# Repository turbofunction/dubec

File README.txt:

Contact:
Janne Savukoski
<firstname>@savukoski.name

                    Part name: DUBEC
                     Revision: 2.3
                   Board size: 40mm x 21.375mm
              Board thickness: 
                   Board type: Four layer
       Outer copper thickness:
       Inner copper thickness:
Solder mask color (top & bot):
 Silkscreen color (top & bot):

No special instructions.

Layer order:

TOP:    DUBEC.toplayer.ger
        DUBEC.internalplane1.ger
        DUBEC.internalplane2.ger
BOTTOM: DUBEC.bottomlayer.ger

Other files:

DUBEC.boardoutline.ger     Outline
DUBEC.topsoldermask.ger    Solder mask TOP
DUBEC.bottomsoldermask.ger Solder mask BOTTOM
DUBEC.topsilkscreen.ger    Silkscreen TOP
DUBEC.bottomsilkscreen.ger Silkscreen BOTTOM
DUBEC.drills.xln           Excellon drill
DUBEC.drl                  Drill rack
DUBEC.tcream.ger           Solder stencil (TOP)

Thank you!

Regards,
Janne Savukoski

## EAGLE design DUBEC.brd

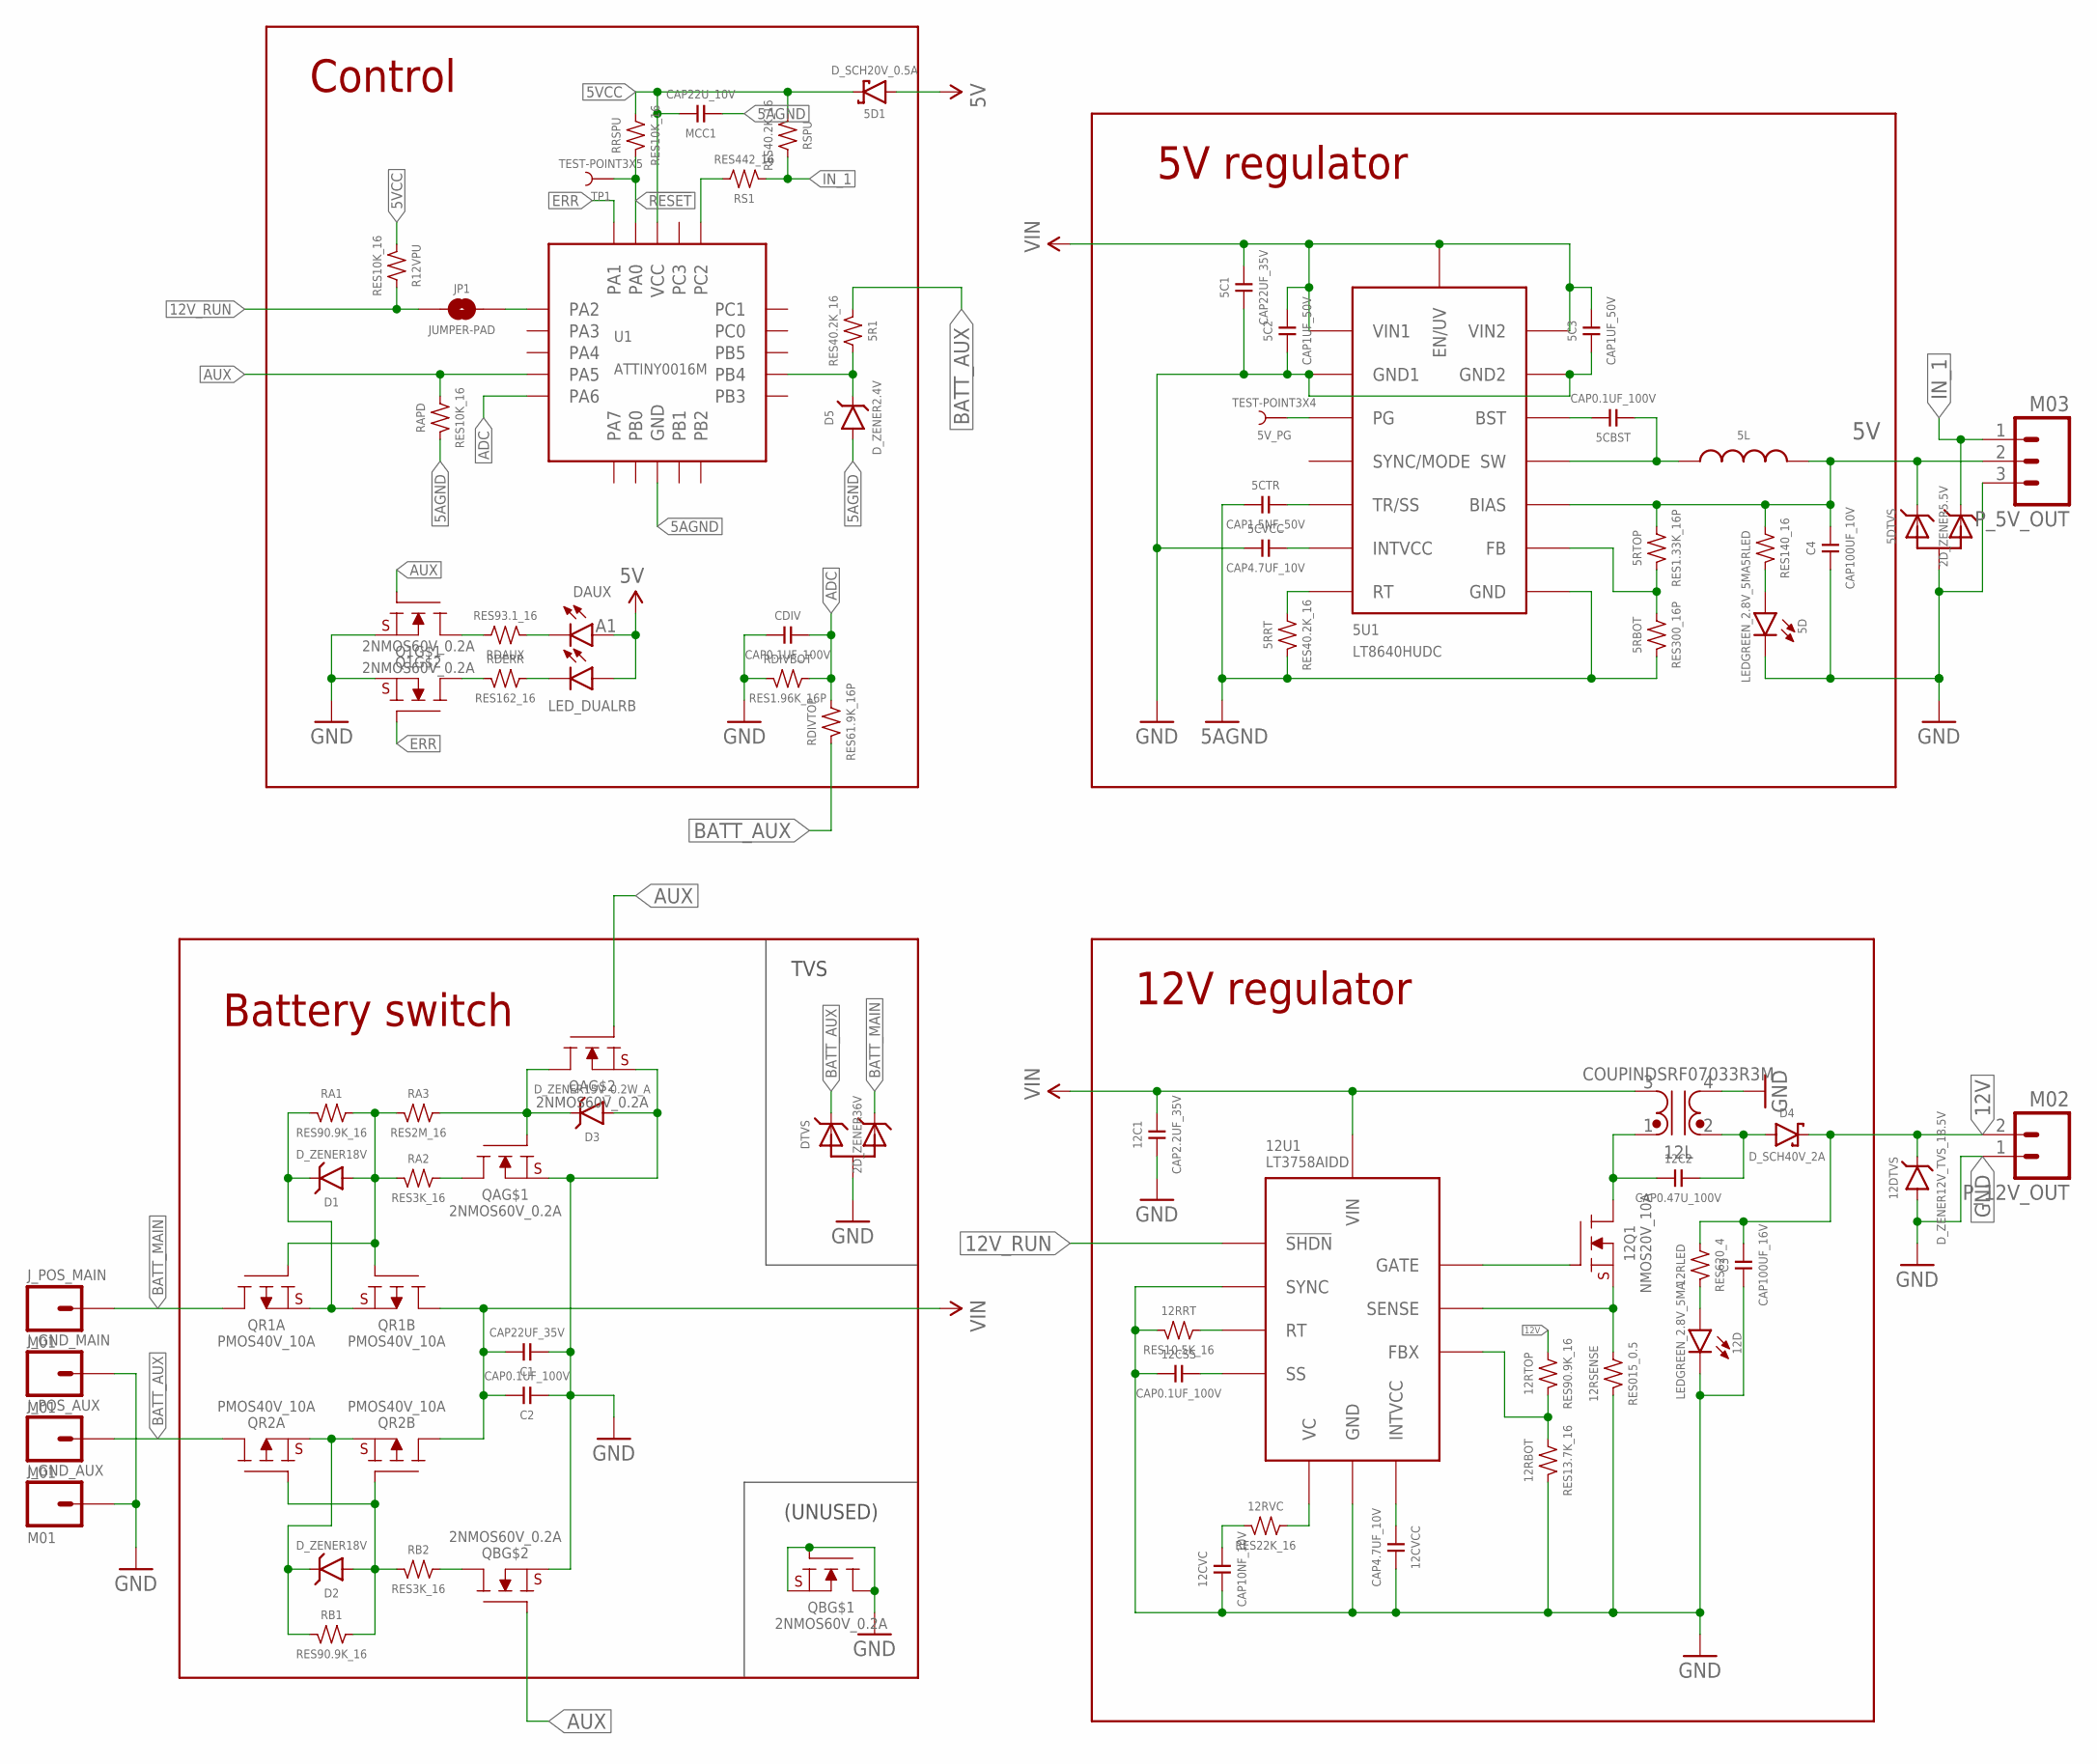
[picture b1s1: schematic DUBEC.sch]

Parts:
5C1: CAP22UF_35V; 0805
5C2, 5C3: CAP1UF_50V; 0603
5CBST, 12CSS: CAP0.1UF_100V; 0402
5CTR: CAP1.5NF_50V; 0402
5CVCC, 12CVCC: CAP4.7UF_10V; 0402
5D, 12D: LEDGREEN_2.8V_5MA; 0603+
5D1: D_SCH20V_0.5A; SOD523+
5DTVS: 2D_ZENER5.5V; SOT23-3
5L: I3.3UH_5A; SRP5030
5R1, 5RRT: RES40.2K_16; 0402
5RBOT: RES300_16P; 0402
5RLED: RES140_16; 0402
5RTOP: RES1.33K_16P; 0402
5U1: LT8640HUDC; QFN-18
5V_PG: TEST-POINT3X4; PAD.03X.04
12C1: CAP2.2UF_35V; 0402
12C2: CAP0.47U_100V; 0805
12CVC: CAP10NF_10V; 0402
12DTVS: D_ZENER12V_TVS_18.5V; SOD323+
12L: COUPINDSRF07033R3M; SRF0703
12Q1: NMOS20V_10A; 6-PQFN
12RBOT: RES13.7K_16; 0402
12RLED: RES620_4; 0603
12RRT: RES10.5K_16; 0402
12RSENSE: RES015_0.5; 1206
12RTOP: RES90.9K_16; 0402
12RVC: RES22K_16; 0402
12U1: LT3758AIDD; DFN-10
C1: CAP22UF_35V; 0805
C2: CAP0.1UF_100V; 0402
C3: CAP100UF_16V; 1210
C4: CAP100UF_10V; 1210
CDIV: CAP0.1UF_100V; 0402
D1, D2: D_ZENER18V; SOD523+
D3: D_ZENER15V_0.2W_A; SOD523+
D4: D_SCH40V_2A; DO-214AC
D5: D_ZENER2.4V; SOD523+
DAUX: LED_DUALRB; 0603+DUAL
DTVS: 2D_ZENER36V; SOT23-3
JP1: JUMPER-PAD; JUMPER-PAD-ROUND
J_GND_AUX: M01; 1X01_NO_SILK
J_GND_MAIN: M01; 1X01_NO_SILK
J_POS_AUX: M01; 1X01_NO_SILK
J_POS_MAIN: M01; 1X01_NO_SILK
MCC1: CAP22U_10V; 0603
P_5V_OUT: M03; 1X03_NO_SILK
P_12V_OUT: M02; 1X02_NO_SILK
Q1: 2NMOS60V_0.2A; SOT-666
QA: 2NMOS60V_0.2A; SOT-666
QB: 2NMOS60V_0.2A; SOT-666
QR1A, QR1B, QR2A, QR2B: PMOS40V_10A; POWERDI3333-8
R12VPU: RES10K_16; 0402
RA1: RES90.9K_16; 0402
RA2: RES3K_16; 0402
RA3: RES2M_16; 0402
RAPD: RES10K_16; 0402
RB1: RES90.9K_16; 0402
RB2: RES3K_16; 0402
RDAUX: RES93.1_16; 0402
RDERR: RES162_16; 0402
RDIVBOT: RES1.96K_16P; 0402
RDIVTOP: RES61.9K_16P; 0402
RRSPU: RES10K_16; 0402
RS1: RES442_16; 0402
RSPU: RES40.2K_16; 0402
TP1: TEST-POINT3X5; PAD.03X.05
U1: ATTINY0016M; 20-VQFN-2

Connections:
5AGND: 5CTR.1, 5RBOT.1, 5RRT.1, 5U1.18 (GND), D5.A, MCC1.1, RAPD.1, U1.3 (GND), U1.PAD (GND)
5V: 5D1.A, 5DTVS.1 (C1), 5L.2, 5RLED.2, 5RTOP.2, 5U1.1 (BIAS), C4.2, DAUX.A1, DAUX.A2, P_5V_OUT.2
5VCC: 5D1.C, MCC1.2, R12VPU.1, RRSPU.2, RSPU.1, U1.4 (VCC)
5V_BST: 5CBST.2, 5U1.3 (BST)
5V_FB: 5RBOT.2, 5RTOP.1, 5U1.20 (FB)
5V_PG: 5U1.19 (PG), 5V_PG.P$1
5V_RT: 5RRT.2, 5U1.15 (RT)
5V_SW: 5CBST.1, 5L.1, 5U1.8-9 (SW), 5U1.21 (SW), 5U1.22 (SW)
5V_TR: 5CTR.2, 5U1.16 (TR/SS)
5V_VCC: 5CVCC.2, 5U1.2 (INTVCC)
12FBX: 12RBOT.2, 12RTOP.1, 12U1.2 (FBX)
12GATE: 12Q1.G, 12U1.7 (GATE)
12INTVCC: 12CVCC.1, 12U1.8 (INTVCC)
12RT: 12RRT.2, 12U1.4 (RT)
12SENSE: 12Q1.S, 12RSENSE.2, 12U1.6 (SENSE)
12SS: 12CSS.2, 12U1.3 (SS)
12V: 12DTVS.C, 12RLED.2, 12RTOP.2, C3.2, D4.C, P_12V_OUT.2
12VC: 12RVC.2, 12U1.1 (VC)
12V_RUN: 12U1.9 (!SHDN), JP1.1, R12VPU.2
!RESET: RRSPU.1, TP1.P$1, U1.19 (PA0)
ADC: CDIV.2, RDIVBOT.2, RDIVTOP.2, U1.7 (PA6)
AUX: Q1.2 (G), QA.5 (G), QB.5 (G), RAPD.2, U1.6 (PA5)
BATT_AUX: 5R1.1, DTVS.1 (C1), J_POS_AUX.1, QR2A.D, RDIVTOP.1
BATT_MAIN: DTVS.2 (C2), J_POS_MAIN.1, QR1A.D
ERR: Q1.5 (G), U1.20 (PA1)
GATE_AUX: D2.A, QR2A.G, QR2B.G, RB1.2, RB2.1
GATE_MAIN: D1.A, QR1A.G, QR1B.G, RA1.2, RA2.1, RA3.1
GATE_MAIN_B: D3.C, QA.2 (G), QA.3 (D), RA3.2
GND: 5C1.1, 5C2.1, 5C3.1, 5CVCC.1, 5D.C, 5DTVS.3 (A), 5U1.6 (GND1), 5U1.7 (GND1), 5U1.10 (GND2), 5U1.11 (GND2), 12C1.1, 12CSS.1, 12CVC.1, 12CVCC.2, 12D.C, 12DTVS.A, 12L.4 (B2), 12RBOT.1, 12RRT.1, 12RSENSE.1, 12U1.5 (SYNC), 12U1.PAD (GND), C1.1, C2.1, C3.1, C4.1, CDIV.1, D3.A, DTVS.3 (A), J_GND_AUX.1, J_GND_MAIN.1, P_5V_OUT.3, P_12V_OUT.1, Q1.1 (S), Q1.4 (S), QA.1 (S), QA.4 (S), QB.1 (S), QB.2 (G), QB.4 (S), QB.6 (D), RDIVBOT.1
IN_1: 5DTVS.2 (C2), P_5V_OUT.1, RS1.1, RSPU.2
LED_BLUE: Q1.6 (D), RDAUX.1
LED_RED: Q1.3 (D), RDERR.2
unnamed: 5R1.2, D5.C, U1.10 (PB4)
unnamed: 5D.A, 5RLED.1
unnamed: RS1.2, U1.17 (PC2)
unnamed: 12D.A, 12RLED.1
unnamed: DAUX.C1, RDAUX.2
unnamed: QA.6 (D), RA2.2
unnamed: QB.3 (D), RB2.2
unnamed: DAUX.C2, RDERR.1
unnamed: 12CVC.2, 12RVC.1
unnamed: 12C2.1, 12L.1 (A1), 12Q1.D
unnamed: 12C2.2, 12L.2 (B1), D4.A
unnamed: JP1.2, U1.1 (PA2)
SRC_AUX: D2.C, QR2A.S, QR2B.S, RB1.1
SRC_MAIN: D1.C, QR1A.S, QR1B.S, RA1.1
VIN: 5C1.2, 5C2.2, 5C3.2, 5U1.4 (VIN1), 5U1.13 (VIN2), 5U1.14 (EN/UV), 12C1.2, 12L.3 (A2), 12U1.10 (VIN), C1.2, C2.2, QR1B.D, QR2B.D

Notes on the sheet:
(UNUSED)
12V regulator
5V regulator
Battery switch
Control
TVS

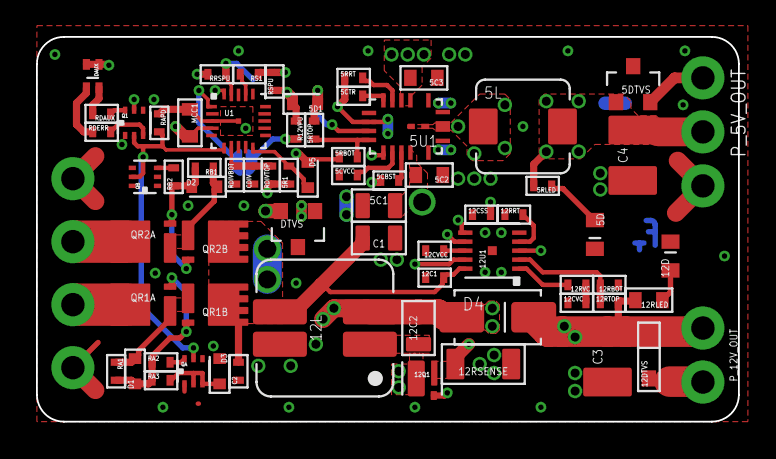
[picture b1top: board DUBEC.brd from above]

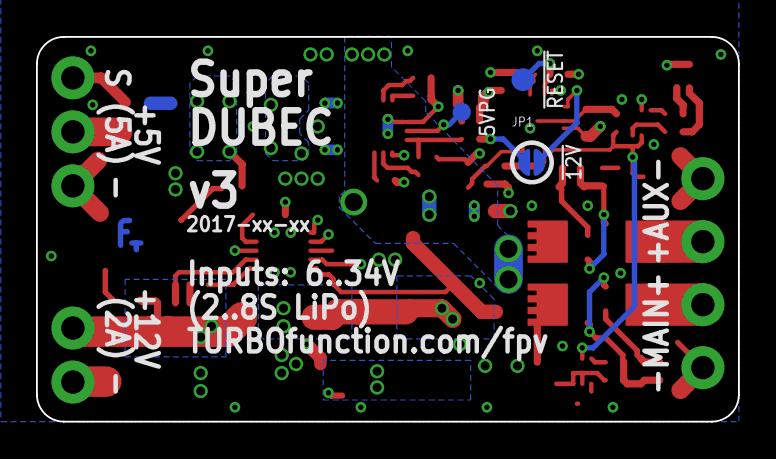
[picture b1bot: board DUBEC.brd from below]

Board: 4 copper layers, 39.0 x 21.4 mm, 77 parts (4 on the bottom side), 47 nets.

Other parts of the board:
U$1: TF-EMBLEM

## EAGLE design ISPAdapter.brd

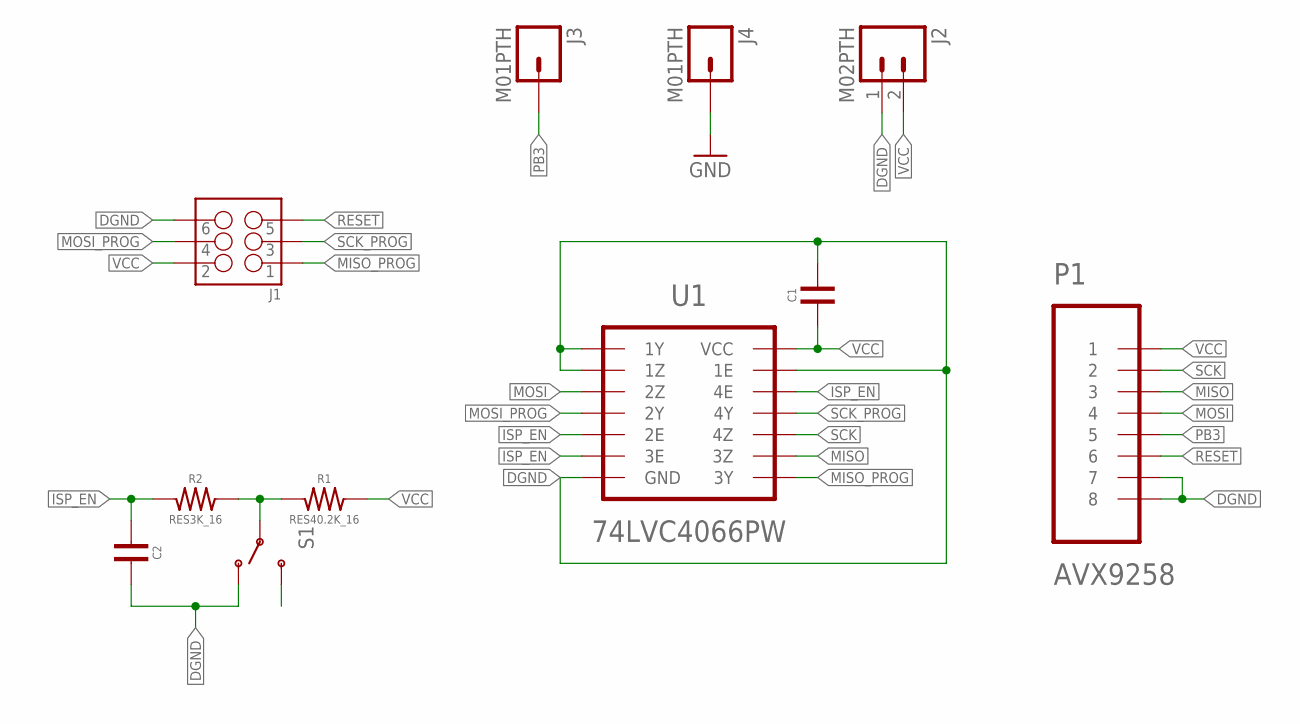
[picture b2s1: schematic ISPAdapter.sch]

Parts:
C1: CAP4.7UF_10V; 0402
C2: CAP0.1UF_100V; 0402
J1: M03X2WR; WR-BHD-3X2
J2: M02PTH; 1X02
J3, J4: M01PTH; 1X01
P1: AVX9258; AVX9258-8C
R1: RES40.2K_16; 0402
R2: RES3K_16; 0402
S1: SWITCH-SPDTESWITCH; EG1271A
U1: 74LVC4066PW; 14-TSSOP

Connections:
DGND: C1.2, C2.2, J1.6, J2.1, P1.7, P1.8, S1.1 (O), S1.4 (O), U1.1 (1Y), U1.2 (1Z), U1.7 (GND), U1.13 (1E)
GND: J4.1
ISP_EN: C2.1, R2.1, U1.5 (2E), U1.6 (3E), U1.12 (4E)
MISO: P1.3, U1.9 (3Z)
MISO_PROG: J1.1, U1.8 (3Y)
MOSI: P1.4, U1.3 (2Z)
MOSI_PROG: J1.4, U1.4 (2Y)
unnamed: S1.3 (S), S1.6 (S)
PB3: J3.1, P1.5
RESET: J1.5, P1.6
SCK: P1.2, U1.10 (4Z)
SCK_PROG: J1.3, U1.11 (4Y)
SWGND: R1.1, R2.2, S1.2, S1.5
VCC: C1.1, J1.2, J2.2, P1.1, R1.2, U1.14 (VCC)

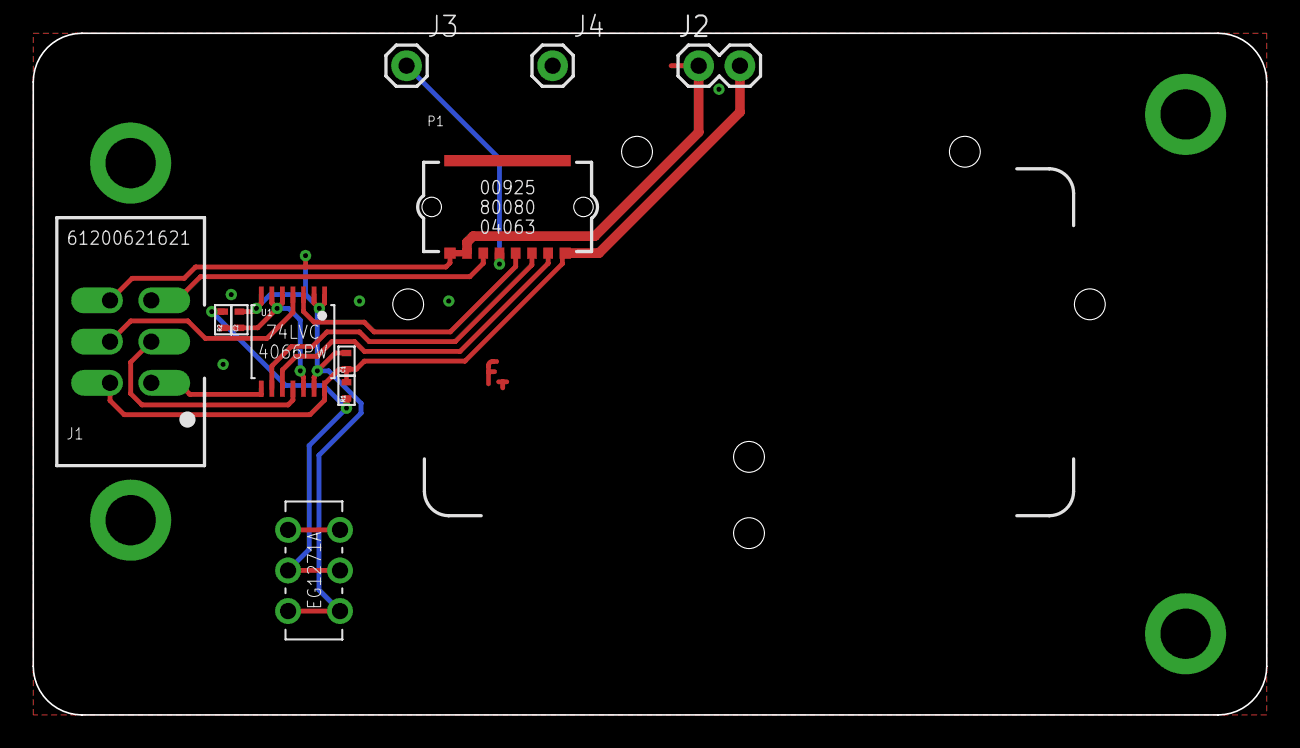
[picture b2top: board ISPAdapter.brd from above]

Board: 2 copper layers, 76.0 x 42.0 mm, 12 parts (0 on the bottom side), 13 nets.

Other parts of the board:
U$2: TF-EMBLEM

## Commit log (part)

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2015-01-15 Component & layout tweaks
2015-01-16 AUX pad
2015-01-17 Tidying
2015-01-17 README version update
2015-01-17 FW tweaks
2015-01-18 Changed couple diodes
2015-01-25 Voltage divider to 1.1V; component optimization; layout tweaks
2015-01-26 README nop
2015-01-26 script tweak
2015-01-27 Layout wanking
2015-01-27 Test-fitting a couple pots
2015-01-27 Revert "Test-fitting a couple pots"
    This reverts commit 098d1195ccc5a94882651b758a5cc31df5305fd6.
2015-01-30 Copper tidying
2015-02-03 High voltage isolation
2015-02-03 Script version bump
2015-02-03 Renames
2015-02-07 Header stops
2015-02-09 Internal ADC ref
2015-02-09 Post-meltdown upgrades: Beefy TVS diode, relay wiring.
2015-02-10 Tuning, tidying
2015-02-10 Proper TVS footprints
2015-02-11 Gilding the lily
2015-02-11 Readme updates
2015-02-11 Tweaked a few land patterns
2015-02-14 Zip version update
2015-02-14 Layout tweaks
2015-02-28 Dropped deprecated comment
2015-02-28 misc. tweaks
2015-02-28 Relay resistor fix
2015-03-01 Tweaks
2015-03-01 Dedicated resistor for AUX testpoint
2015-03-01 BOM optimization
2015-03-05 wank
2015-03-09 Two-color AUX LED
2015-03-14 Adjusted led resistors
2015-03-15 Smaller pads
2015-04-06 Logo draft
2015-04-06 Added snubber cap
2015-04-11 Snubber placement
2015-04-12 Schema png
2015-04-13 Relay resistor update; cream tweaks
2015-04-14 Dropped relay diode
2015-04-15 MOSFET "relay" spice model working!
2015-04-15 Being discreet. https://www.youtube.com/watch?v=mkBu_pAkYYg
2015-04-17 Trying to get the gates to ground..
2015-04-17 SPICE model works!
2015-04-19 Switch to MOSFET "relay"
2015-04-19 Fixed one schematic error
2015-04-21 1.3 ready?
2015-04-21 Resistor tweaks
2015-04-21 ShenZhen2U file naming
2015-04-21 Updated schema export
2015-04-21 mkzip tweak
2015-04-28 Tidying; cap package; LED resistor update
2015-04-28 Version bump
2015-04-28 Tidying schematic
2015-05-12 12V RUN toggle
2015-05-13 SPICE: tweaked a couple resistors
2015-05-13 12V run pull-up
2015-05-13 Solder jump for 12v run
2015-07-24 LTSpice model tweak
2015-10-25 Drafting small ISP header
2015-10-29 Wired new ISP pads
2015-10-30 tidy
2015-10-31 Restored output bypass caps
2015-11-01 ISP adapter board
2015-11-01 Tweaks; scripts updates
2015-11-01 CAM tidying
2015-11-01 .gitignore
2015-11-02 Dropped ground layer
2015-11-02 Grounded screw holes; disconnected unused connector pins
2015-11-02 Gate bias from output
2015-11-02 Revert "Gate bias from output"
    This reverts commit 8d7e7a652f864d48bba04cdb831ad6f39832c5c0.
2015-11-02 Gate bias from source
2015-11-03 Upped resistors, tweaked phases
2015-11-03 Upped switch resistors
2015-11-03 Kelvin join?
2015-11-04 Voltage divider tweak
2015-11-04 Fault LED control
2015-11-04 Warn blink
2015-11-04 warn voltage calculation
2015-11-04 Battery disconnect pin change interrupt
2015-11-04 Toggle 12V
2015-11-05 Voltage divider to 4.6V
2015-11-05 Voltage divider to 4.7V
2015-11-05 Reset pull-up
2015-11-05 Ground plane bottom
2015-11-09 Bugfixes
2015-11-13 IN pull-down instead of pull-up
2015-11-13 Revert "IN pull-down instead of pull-up"
    This reverts commit 7647d503c6cdeac1e35f886be3c611ab72df0953.
2015-11-16 Zip version bump
2015-11-16 IN pull-up fix
2015-11-17 Updated resistors
2015-11-17 Firmware tweaks
2015-11-17 Firmware tweak
2015-11-18 Fallback logic fix
2015-11-18 Emblem to library; tweaks
2015-11-18 Updated schema image export
2015-11-18 AUX divider update (due to non-stock)
2015-11-18 Firmware ADC fix
2015-11-20 Board fixes and isolation
2015-11-20 Board export
2015-11-23 Bored wanking
2015-11-24 Kelvinize
2015-11-24 More proper kelvining. Better be stable now...
2015-11-24 Kelvinized 5V as well
2015-11-25 Removed too small mask stop elements
2015-11-26 SMD pad tweaks
2015-11-26 Upped LED currents to 15mA
2015-11-26 Fault LED wiring update
2015-11-27 Paste footprint updates
2015-11-29 ignore *.lck
2015-11-29 Output low by toggling direction
2015-11-29 ADC averaging
2015-11-29 Weaker signal pull-up
2015-11-30 8-bit ADC resolution to save program space
2015-11-30 More grounding
2015-12-01 Fixes to voltage average handling
2015-12-01 Restructuring
2015-12-01 Back to full ADC resolution; forgot that 256-bit resolution of 33.6V would be a whopping 131mV
2015-12-02 Updated battery diodes
2015-12-03 Cleared out interrupt handler code
2015-12-04 Noob bugfix; signal level mapping
2015-12-04 Bugfix revert; I misread the assembler, it was correct after all. Also, let the compiler calculate the MIN_VOLTAGE.
2015-12-04 Typo fix
2015-12-06 Separate connector mounting pad
2015-12-06 Tweak
2015-12-06 Larger annular
2015-12-08 Added PB3 (AUX) to header for HVSP; adjusted LED resistors
2015-12-08 Angled diodes, TODO snubber-RC
2015-12-08 More suitable diode
2015-12-09 Firmware: v1.4 red LED wiring
2015-12-10 RC snubber
2015-12-13 Snubber tweak
2015-12-13 NMOS to replace diode
2015-12-13 Revert "NMOS to replace diode"
    This reverts commit b5f679a1d9c1df25f2a9366656623a2bb0e6c105.
2015-12-13 Replaced diode with a solder pad
2015-12-13 Pin change at 2.5V, can't use for battery detection. Thus, ADC ref to 1.1V.
2015-12-14 Adapter wiring to match DUBEC 1.5
2015-12-14 ISP/DW-switch
2015-12-15 Changed switch IC
2015-12-15 Switch IC fitting
2015-12-15 ISP labeling
2015-12-15 Full PCB pattern for connector
2015-12-15 Full connector mapping
2015-12-16 Added cap to switch
2015-12-16 Moved solder pad to bottom
2015-12-16 TSSOP
2015-12-17 Layout updates, land pattern tweaks
2015-12-17 Land pattern tweaks
2015-12-18 Limited LED currents
2015-12-18 Faster disconnect detection
2015-12-20 Jack/Plug refs; offset pads
2015-12-21 Red-Blue status LED
2015-12-21 More consistent LED wiring
2015-12-22 FET driver for status led
2015-12-22 Status LED resistors; tidy
2015-12-22 Status LED to 20mA
2016-02-10 Commit date
2016-02-10 README revisions
2016-02-10 Adapter zip revision
2016-02-10 Layout tidy
2016-02-15 Minor tidy
2016-02-24 Device param update
2016-02-24 5V regulator update; inductors from digikey
2016-02-24 Inductor footprint check
2016-02-24 More heat sinking
2016-02-26 5V configured to Forced Continuous mode
2016-02-28 Bourns inductors
2016-02-28 Ground plane fix; tidy
2016-02-28 Restored MCU diode; couldn't recall any reason to avoid it now that using 1.1V as ADC reference
2016-02-28 Dropped VCC jumper pad; cleanup
2016-03-01 Corrected hole position
2016-03-01 Tidying based on proto
2016-03-01 Moved hole and tightened dia to 1.9mm
2016-03-01 Mask stop tweaks
2016-03-01 12V reg pad simplification and tweaks. Also to analog ground <- not sure if a good idead.
2016-03-02 redo 12V reg pad mask & cream
2016-03-08 DRC fixes; tidy
2016-03-08 Kelvin MCU to 5V ground
2016-03-10 Schema PNG update
2016-03-13 Tweaks; date
2016-03-13 Revision
2016-03-13 Adjusted drills; date
2016-03-13 .gpi comment
2016-03-13 Added solder stencil
2016-03-14 Added some labels
2016-03-14 Updated dates
2016-03-14 Rev bump
2016-03-16 Solder stencil fixes
2016-03-24 HVSP table
2016-03-24 Spacing
2016-03-25 Default set of visible layers
2016-03-25 Deja vu: replaced MCU diode with a jumper pad
2016-03-26 Cleanup
2016-03-26 Pin order change
2016-03-26 Default visible layers
2016-03-29 Metric traces (wank)
2016-03-29 Metric traces
2016-03-31 Text move
2016-04-04 Draft: replace diodes with mosfets
2016-04-05 Laying out the mosfet switch
2016-04-05 Switch layouting
2016-04-05 Replaced diodes with fets
2016-04-05 Excess board space? Drill a hole.
2016-04-05 Added spot for another snubber cap
2016-04-06 Dual 5V TVS diode
2016-04-06 Updated TVS diodes
2016-04-08 Batt input TVS diode
2016-04-10 More rational voltage divider
2016-04-10 Voltage divider to 1.1V. Cleanup.
2016-04-11 ADC divider now to 1.1V. Previous commit was the 5V divider...
2016-04-15 Tweaks, date
2016-04-15 Post-order revision bump
2016-04-20 Debounce, grounding
2016-04-25 Tweaks, tidy
2016-05-30 AUX wiring update
2016-05-30 Bugfix, updated comments
2016-05-30 Enlarged a couple current paths
2016-05-30 More cream!
2016-05-30 ADC calibration
2016-07-16 Added 12V ramp-up switch
2016-07-16 FET update, tidy
2016-07-17 12V soft-start load switch
2016-07-17 Labels
2016-07-17 Simulation timing
2016-07-17 Compacting
2016-07-17 Loop fix, tweaks
2016-07-17 12V output cap placement
2016-07-17 Bigger screw holes, tidy
2016-07-17 Version bump; bottom silk adjust
2016-07-17 Contact info cleanup
2016-07-17 Schema export update
2016-07-18 Adjusted inductor land pattern
2016-07-18 DUBEC v2.0 schema export
2016-07-18 Label change
2016-07-18 Another label change
2016-07-19 Tiny fix
2016-07-20 LTC3115-1 with load switch
2016-07-20 12V TVS diode update
2016-07-25 Package fix
2016-08-13 Component tweaks
2016-08-15 FET change
2016-08-15 Zener update
2016-08-16 Layout tweak
2016-08-16 12V led to actual output
2016-08-22 EMC tweaks
2016-08-22 EMC tweaks etc.
2016-08-25 Power trace update
2016-08-29 Proper 12V load switch
2016-08-29 Schema tidy
2016-09-04 OSH Park CAM; many tweak
2016-09-04 .gitignore update
2016-09-04 No bottom cream
2016-09-05 zip update
2016-09-27 Solder stop margins, due to OSHPark reg error
2016-11-16 layer 108
2016-11-16 catch-up
2017-07-31 LT3758 spice model
2017-07-31 LT3758
2017-07-31 LT8710
2017-07-31 Python script to list constant power resistance values
2017-07-31 Started converting to LT3758A
2017-08-03 script update
2017-08-03 spice updates
2017-08-03 v3 finished
2017-08-22 ATtiny1616
2017-08-22 Rerouting
2017-08-22 Removed a 2-layer DRU
2017-08-23 Rework finished?
2017-08-28 Fitting better FETs
2017-08-28 FET change complete
2017-08-30 MOS type correction
2017-08-31 Ok, keeping it safe.. (dropped the grounding of NC MCU pins)

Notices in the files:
parts and their libraries:
SparkFun-Passives: Licensing: Creative Commons ShareAlike 4.0 International - https://creativecommons.org/licenses/by-sa/4.0
